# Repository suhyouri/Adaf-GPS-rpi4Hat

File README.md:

# Adaf-GPS-rpi4Hat
<br>
rpi4Hat for Adafruit Ultimate GPS, DC-DC converter 12V to 5V, PIC16F18325 <br>
<br>
Adafruit Ultimate GPS Breakout - 66 channel w/10 Hz updates - PA1616S https://www.adafruit.com/product/746 
<br>
[gps-power_sch.pdf](https://github.com/suhyouri/Adaf-GPS-rpi4Hat/files/7948000/gps-power_sch.pdf)<br>
[gps-power_brd.pdf](https://github.com/suhyouri/Adaf-GPS-rpi4Hat/files/7948001/gps-power_brd.pdf)<br>
<br>

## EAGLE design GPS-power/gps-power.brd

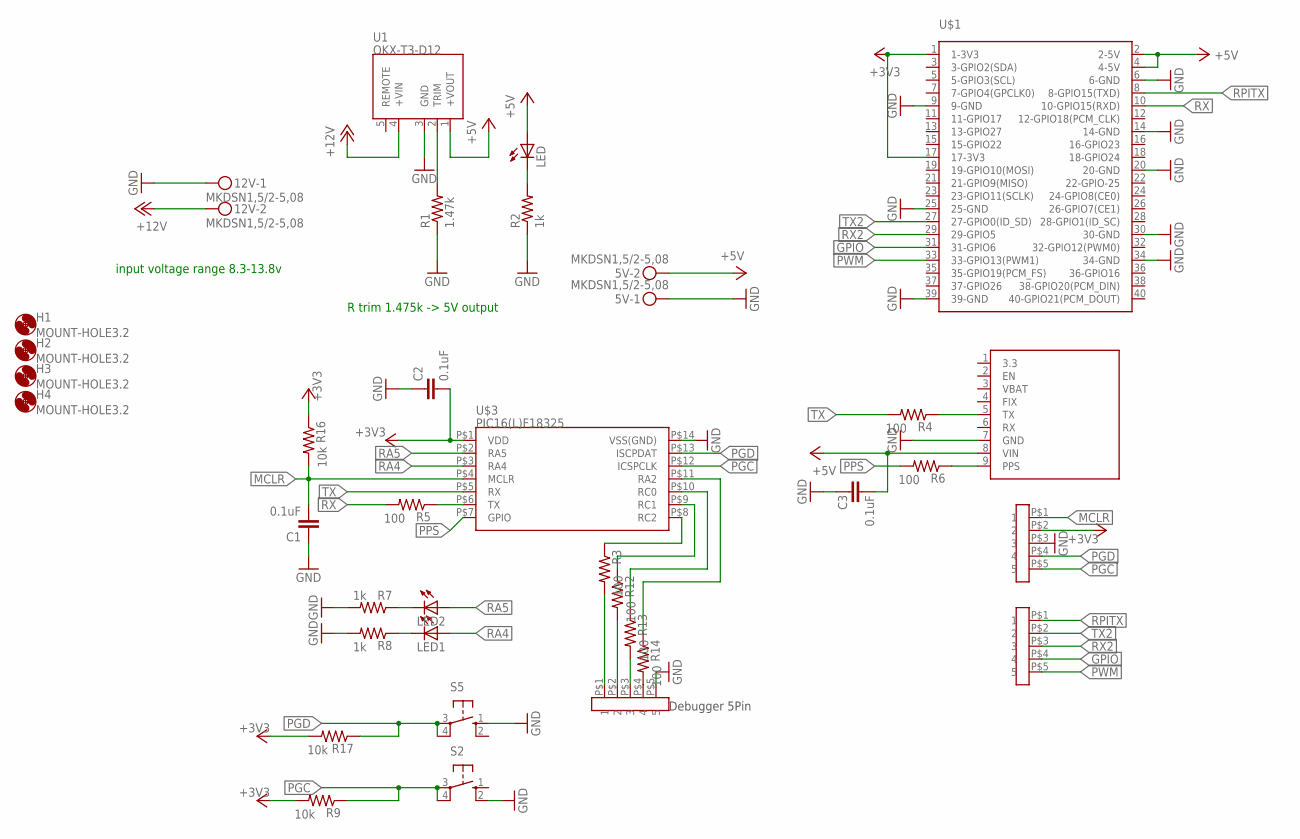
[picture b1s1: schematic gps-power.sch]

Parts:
5V, 12V: MKDSN1,5/2-5,08
8,9,10,11,GND: PIN-5
C1, C2, C3: 0.1uF; 0603
GND: PIN-5
H1, H2, H3, H4: MOUNT-HOLE3.2; 3,2
LED, LED1, LED2: LEDCHIPLED_0603; CHIPLED_0603
MPLAB: PIN-5
R1: 1.47k; R0603
R2, R7, R8: 1k; R0603
R3, R4, R5, R6, R12, R13, R14: 100; R0603
R9, R16, R17: 10k; R0603
S2, S5: 10-XX; B3F-10XX
U1: OKX-T3-D12
U$1: GPIO-HD-2X20
U$2: ADA-GPS
U$3: PIC16(L)F18325; DIP-S-14

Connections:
+3V3: C2.2, MPLAB.P$2 (2), R9.2, R16.1, R17.2, U$1.1 (1-3V3), U$1.17 (17-3V3), U$3.P$1 (VDD)
+5V: 5V.2, C3.2, LED.A, U1.1 (+VOUT), U$1.2 (2-5V), U$1.4 (4-5V), U$2.8 (VIN)
+12V: 12V.2, U1.4 (+VIN)
GND: 5V.1, 8,9,10,11,GND.P$5 (5), 12V.1, C1.1, C2.1, C3.1, MPLAB.P$3 (3), R1.1, R2.1, R7.2, R8.2, S2.2 (S1), S5.1 (S), U1.3 (GND), U$1.6 (6-GND), U$1.9 (9-GND), U$1.14 (14-GND), U$1.20 (20-GND), U$1.25 (25-GND), U$1.30 (30-GND), U$1.34 (34-GND), U$1.39 (39-GND), U$2.7 (GND), U$3.P$14 (VSS(GND))
GPIO: GND.P$4 (4), U$1.31 (31-GPIO6)
MCLR: C1.2, MPLAB.P$1 (1), R16.2, U$3.P$4 (MCLR)
unnamed: 8,9,10,11,GND.P$4 (4), R14.2
unnamed: R5.1, U$3.P$6 (TX)
unnamed: LED.C, R2.2
unnamed: LED2.C, R7.1
unnamed: R3.1, U$3.P$8 (RC2)
unnamed: R6.1, U$2.9 (PPS)
unnamed: R12.1, U$3.P$9 (RC1)
unnamed: R4.1, U$2.5 (TX)
unnamed: LED1.C, R8.1
unnamed: R13.1, U$3.P$10 (RC0)
unnamed: R14.1, U$3.P$11 (RA2)
unnamed: 8,9,10,11,GND.P$1 (1), R3.2
unnamed: 8,9,10,11,GND.P$2 (2), R12.2
unnamed: 8,9,10,11,GND.P$3 (3), R13.2
PGC: MPLAB.P$5 (5), R9.1, S2.3, S2.4 (P1), U$3.P$12 (ICSPCLK)
PGD: MPLAB.P$4 (4), R17.1, S5.3, S5.4 (P1), U$3.P$13 (ISCPDAT)
PPS: R6.2, U$3.P$7 (GPIO)
PWM: GND.P$5 (5), U$1.33 (33-GPIO13(PWM1))
RA4: LED1.A, U$3.P$3 (RA4)
RA5: LED2.A, U$3.P$2 (RA5)
RPITX: GND.P$1 (1), U$1.8 (8-GPIO15(TXD))
RX: R5.2, U$1.10 (10-GPIO15(RXD))
RX2: GND.P$3 (3), U$1.29 (29-GPIO5)
TRIM: R1.2, U1.2 (TRIM)
TX: R4.2, U$3.P$5 (RX)
TX2: GND.P$2 (2), U$1.27 (27-GPIO0(ID_SD))

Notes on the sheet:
R trim 1.475k -> 5V output
input voltage range 8.3-13.8v
Debugger 5Pin

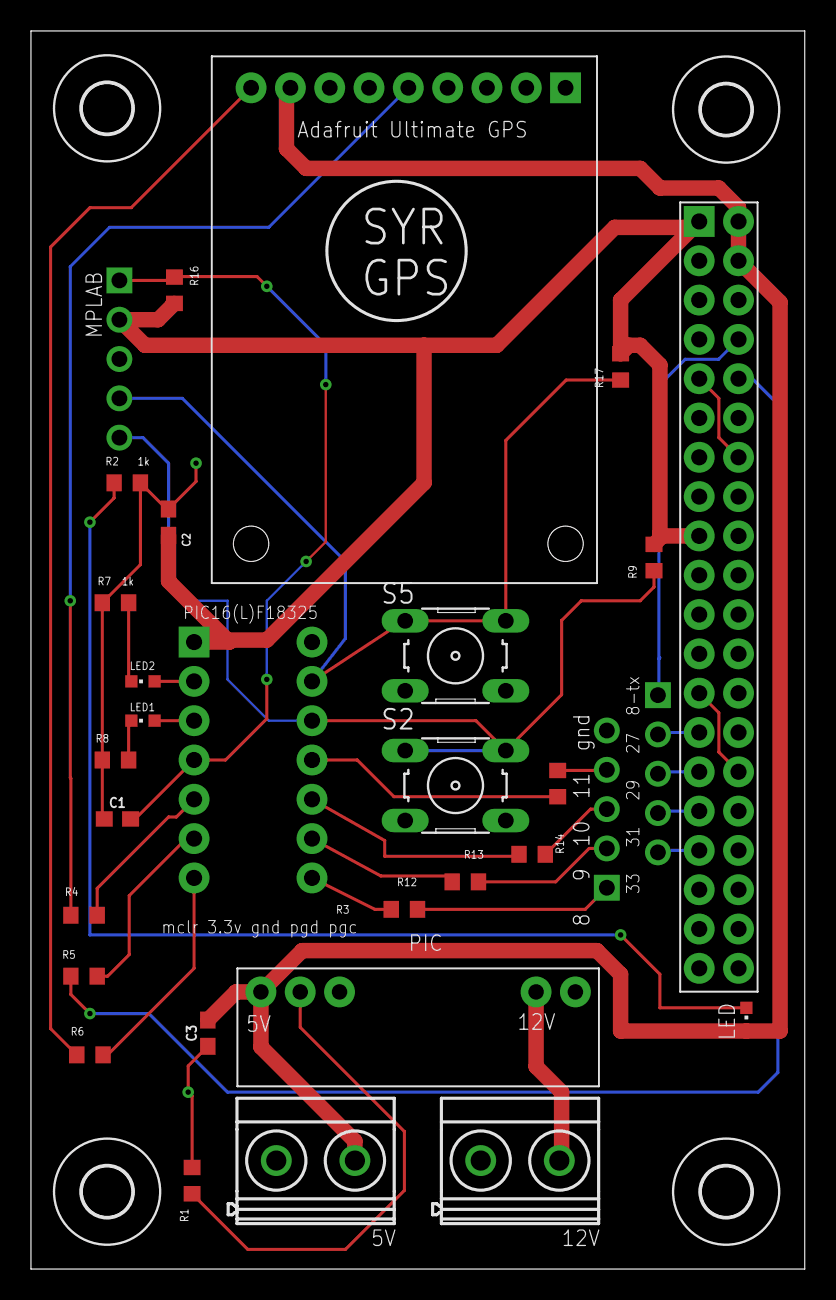
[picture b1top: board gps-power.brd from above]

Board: 2 copper layers, 50.0 x 80.0 mm, 35 parts (0 on the bottom side), 32 nets.

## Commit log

2022-01-27 GPS Eagle Sch,brd Design
2022-02-01 soojeong~

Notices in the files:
parts and their libraries:
SparkFun-Capacitors: Licensing: Creative Commons ShareAlike 4.0 International - https://creativecommons.org/licenses/by-sa/4.0
